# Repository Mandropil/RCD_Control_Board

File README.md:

# RCD_Control_Board
18 Channel PCB with Arduino,  BLE Module, analogue dimming and Cordova App

The board found in the folder "Lichtkasten" can drive up to 18 channels of LED 
with a current limited only by the RCD drivers installed (370ma and 700ma tested) 

The Arduino Nano is driving 3 6 way digital pots with a scale of 256 positions each. 

Digital pots are used for getting non PWM and thus not pulsing lights. 

When the power source is clean, the LEDs are driven wit constand current. 

The <b>AD5206</b> is a 6 channel potentiometer with SPI interface

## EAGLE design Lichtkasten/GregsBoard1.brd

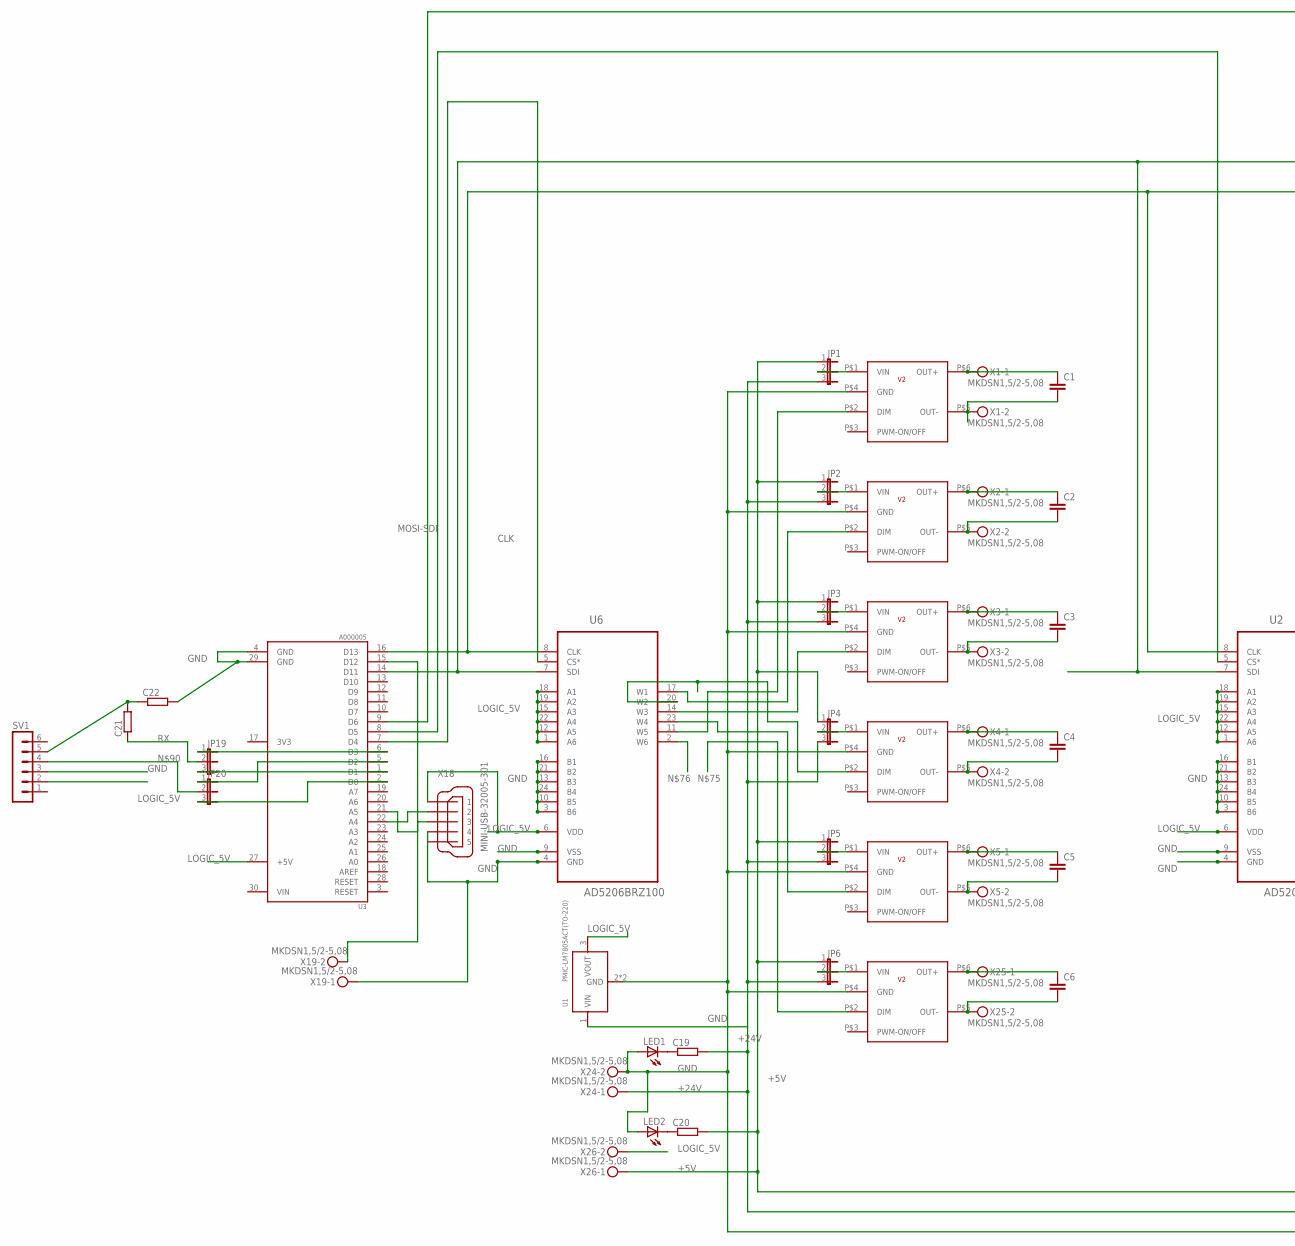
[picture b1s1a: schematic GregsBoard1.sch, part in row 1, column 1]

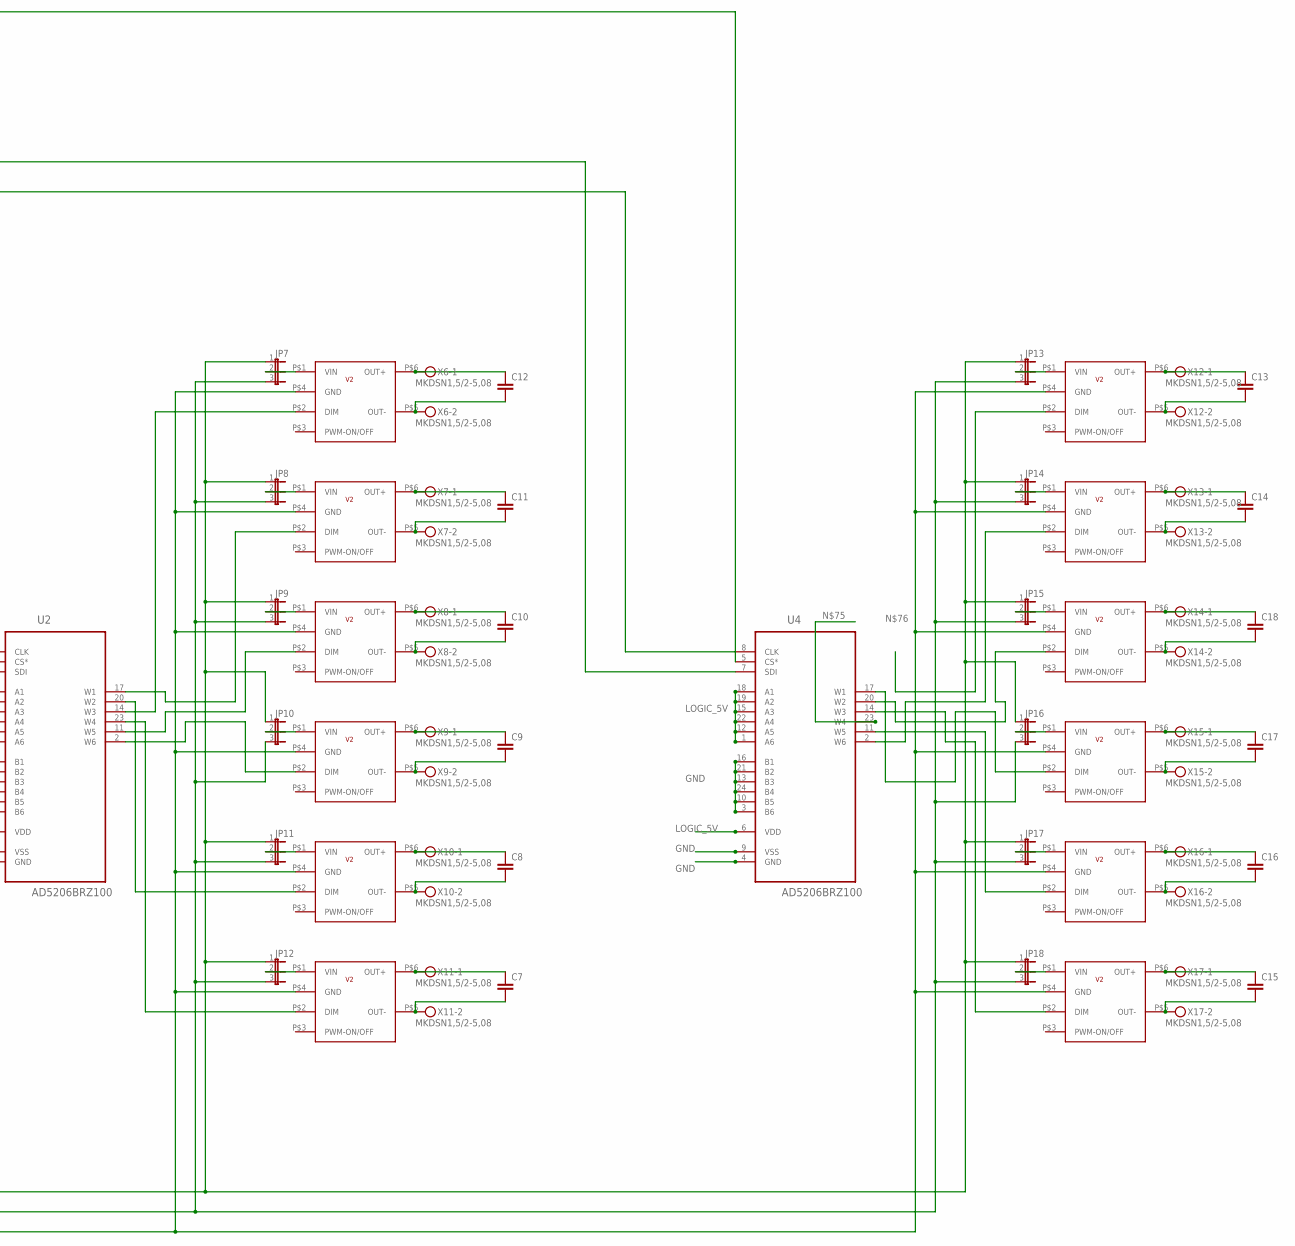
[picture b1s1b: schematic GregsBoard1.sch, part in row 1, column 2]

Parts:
C1, C2, C3, C4, C5, C6, C7, C8, C9, C10, C11, C12, C13, C14, C15, C16, C17, C18: C-EU050-045X075; C050-045X075
C19, C20, C21, C22: R-EU_0207/7; 0207/7
IC1, IC2, IC3, IC4, IC5, IC6, IC7, IC8, IC9, IC10, IC11, IC12, IC13, IC14, IC15, IC16, IC17, IC18: RCD-24_MY_DEV; RCD24-DIP
JP1, JP2, JP3, JP4, JP5, JP6, JP7, JP8, JP9, JP10, JP11, JP12, JP13, JP14, JP15, JP16, JP17, JP18, JP19, JP20: JP2E; JP2
LED1, LED2: LEDB152; Q62902-B152
SV1: MA06-1
U1: PMIC-LM7805ACT(TO-220); TO-220
U2, U4, U6: AD5206BRZ100; SOIC127P1032X265-24N
U3: A000005; ARDUINO_A000005
X1, X2, X3, X4, X5, X6, X7, X8, X9, X10, X11, X12, X13, X14, X15, X16, X17, X19, X24, X25, X26: MKDSN1,5/2-5,08
X18: MINI-USB-32005-301; 32005-301

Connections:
+5V: C20.2, JP1.1, JP2.1, JP3.1, JP4.1, JP5.1, JP6.1, JP7.1, JP8.1, JP9.1, JP10.1, JP11.1, JP12.1, JP13.1, JP14.1, JP15.1, JP16.1, JP17.1, JP18.1, X26.1
+24V: C19.2, JP1.3, JP2.3, JP3.3, JP4.3, JP5.3, JP6.3, JP7.3, JP8.3, JP9.3, JP10.3, JP11.3, JP12.3, JP13.3, JP14.3, JP15.3, JP16.3, JP17.3, JP18.3, U1.1 (VIN), X24.1
CLK: U2.8 (CLK), U3.16 (D13), U4.8 (CLK), U6.8 (CLK)
GND: C22.2, IC1.P$4 (GND), IC2.P$4 (GND), IC3.P$4 (GND), IC4.P$4 (GND), IC5.P$4 (GND), IC6.P$4 (GND), IC7.P$4 (GND), IC8.P$4 (GND), IC9.P$4 (GND), IC10.P$4 (GND), IC11.P$4 (GND), IC12.P$4 (GND), IC13.P$4 (GND), IC14.P$4 (GND), IC15.P$4 (GND), IC16.P$4 (GND), IC17.P$4 (GND), IC18.P$4 (GND), LED1.A, LED2.A, SV1.3, U1.2 (GND), U1.HEAT (GND), U2.3 (B6), U2.4 (GND), U2.9 (VSS), U2.10 (B5), U2.13 (B3), U2.16 (B1), U2.21 (B2), U2.24 (B4), U3.4 (GND), U3.29 (GND), U4.3 (B6), U4.4 (GND), U4.9 (VSS), U4.10 (B5), U4.13 (B3), U4.16 (B1), U4.21 (B2), U4.24 (B4), U6.3 (B6), U6.4 (GND), U6.9 (VSS), U6.10 (B5), U6.13 (B3), U6.16 (B1), U6.21 (B2), U6.24 (B4), X18.4, X19.1, X24.2
LOGIC_5V: SV1.2, U1.3 (VOUT), U2.1 (A6), U2.6 (VDD), U2.12 (A5), U2.15 (A3), U2.18 (A1), U2.19 (A2), U2.22 (A4), U3.27 (+5V), U4.1 (A6), U4.6 (VDD), U4.12 (A5), U4.15 (A3), U4.18 (A1), U4.19 (A2), U4.22 (A4), U6.1 (A6), U6.6 (VDD), U6.12 (A5), U6.15 (A3), U6.18 (A1), U6.19 (A2), U6.22 (A4), X18.1, X26.2
MOSI-SDI: U2.7 (SDI), U3.14 (D11), U4.7 (SDI), U6.7 (SDI)
unnamed: C6.1, IC1.P$6 (OUT+), X25.1
unnamed: C6.2, IC1.P$5 (OUT-), X25.2
unnamed: C1.1, IC2.P$6 (OUT+), X1.1
unnamed: C1.2, IC2.P$5 (OUT-), X1.2
unnamed: C2.1, IC3.P$6 (OUT+), X2.1
unnamed: C2.2, IC3.P$5 (OUT-), X2.2
unnamed: C3.1, IC4.P$6 (OUT+), X3.1
unnamed: C3.2, IC4.P$5 (OUT-), X3.2
unnamed: C4.1, IC5.P$6 (OUT+), X4.1
unnamed: C4.2, IC5.P$5 (OUT-), X4.2
unnamed: C5.1, IC6.P$6 (OUT+), X5.1
unnamed: C5.2, IC6.P$5 (OUT-), X5.2
unnamed: IC2.P$2 (DIM), U6.11 (W5)
unnamed: IC3.P$2 (DIM), U6.17 (W1)
unnamed: IC4.P$2 (DIM), U6.14 (W3)
unnamed: IC5.P$2 (DIM), U6.20 (W2)
unnamed: IC6.P$2 (DIM), U6.23 (W4)
unnamed: U3.22 (A4), X18.2
unnamed: IC2.P$1 (VIN), JP1.2
unnamed: IC3.P$1 (VIN), JP2.2
unnamed: IC4.P$1 (VIN), JP3.2
unnamed: IC5.P$1 (VIN), JP4.2
unnamed: IC6.P$1 (VIN), JP5.2
unnamed: IC1.P$1 (VIN), JP6.2
unnamed: U3.7 (D4), U6.5 (CS*)
unnamed: U2.5 (CS*), U3.8 (D5)
unnamed: C12.1, IC7.P$6 (OUT+), X6.1
unnamed: C12.2, IC7.P$5 (OUT-), X6.2
unnamed: C11.1, IC8.P$6 (OUT+), X7.1
unnamed: C11.2, IC8.P$5 (OUT-), X7.2
unnamed: C10.1, IC9.P$6 (OUT+), X8.1
unnamed: C10.2, IC9.P$5 (OUT-), X8.2
unnamed: C9.1, IC10.P$6 (OUT+), X9.1
unnamed: C9.2, IC10.P$5 (OUT-), X9.2
unnamed: C8.1, IC11.P$6 (OUT+), X10.1
unnamed: C8.2, IC11.P$5 (OUT-), X10.2
unnamed: C7.1, IC12.P$6 (OUT+), X11.1
unnamed: C7.2, IC12.P$5 (OUT-), X11.2
unnamed: IC7.P$2 (DIM), U2.14 (W3)
unnamed: IC8.P$2 (DIM), U2.17 (W1)
unnamed: IC9.P$2 (DIM), U2.11 (W5)
unnamed: IC10.P$2 (DIM), U2.2 (W6)
unnamed: IC11.P$2 (DIM), U2.20 (W2)
unnamed: IC12.P$2 (DIM), U2.23 (W4)
unnamed: IC7.P$1 (VIN), JP7.2
unnamed: IC8.P$1 (VIN), JP8.2
unnamed: IC9.P$1 (VIN), JP9.2
unnamed: IC10.P$1 (VIN), JP10.2
unnamed: IC11.P$1 (VIN), JP11.2
unnamed: IC12.P$1 (VIN), JP12.2
unnamed: U3.9 (D6), U4.5 (CS*)
unnamed: C18.1, IC15.P$6 (OUT+), X14.1
unnamed: C13.1, IC13.P$6 (OUT+), X12.1
unnamed: C13.2, IC13.P$5 (OUT-), X12.2
unnamed: C14.1, IC14.P$6 (OUT+), X13.1
unnamed: C14.2, IC14.P$5 (OUT-), X13.2
unnamed: C18.2, IC15.P$5 (OUT-), X14.2
unnamed: C17.1, IC16.P$6 (OUT+), X15.1
unnamed: C17.2, IC16.P$5 (OUT-), X15.2
unnamed: U3.15 (D12), X19.2
unnamed: C16.1, IC17.P$6 (OUT+), X16.1
unnamed: C16.2, IC17.P$5 (OUT-), X16.2
unnamed: C15.1, IC18.P$6 (OUT+), X17.1
unnamed: C15.2, IC18.P$5 (OUT-), X17.2
unnamed: U3.21 (A5), X18.3
unnamed: IC14.P$2 (DIM), U4.2 (W6)
unnamed: IC15.P$2 (DIM), U4.20 (W2)
unnamed: IC16.P$2 (DIM), U4.17 (W1)
unnamed: IC17.P$2 (DIM), U4.11 (W5)
unnamed: IC18.P$2 (DIM), U4.14 (W3)
unnamed: IC13.P$1 (VIN), JP13.2
unnamed: IC14.P$1 (VIN), JP14.2
unnamed: C19.1, LED1.K (C)
unnamed: C20.1, LED2.K (C)
unnamed: IC1.P$2 (DIM), U4.23 (W4)
unnamed: IC13.P$2 (DIM), U6.2 (W6)
unnamed: IC15.P$1 (VIN), JP15.2
unnamed: IC16.P$1 (VIN), JP16.2
unnamed: IC17.P$1 (VIN), JP17.2
unnamed: IC18.P$1 (VIN), JP18.2
unnamed: JP19.3, U3.1 (D1)
unnamed: JP19.1, U3.6 (D3)
unnamed: C21.1, JP19.2
unnamed: JP20.1, U3.5 (D2)
unnamed: JP20.2, SV1.4
RX: C21.2, C22.1, SV1.5
TX: JP20.3, U3.2 (D0)
VIN: U3.30 (VIN)

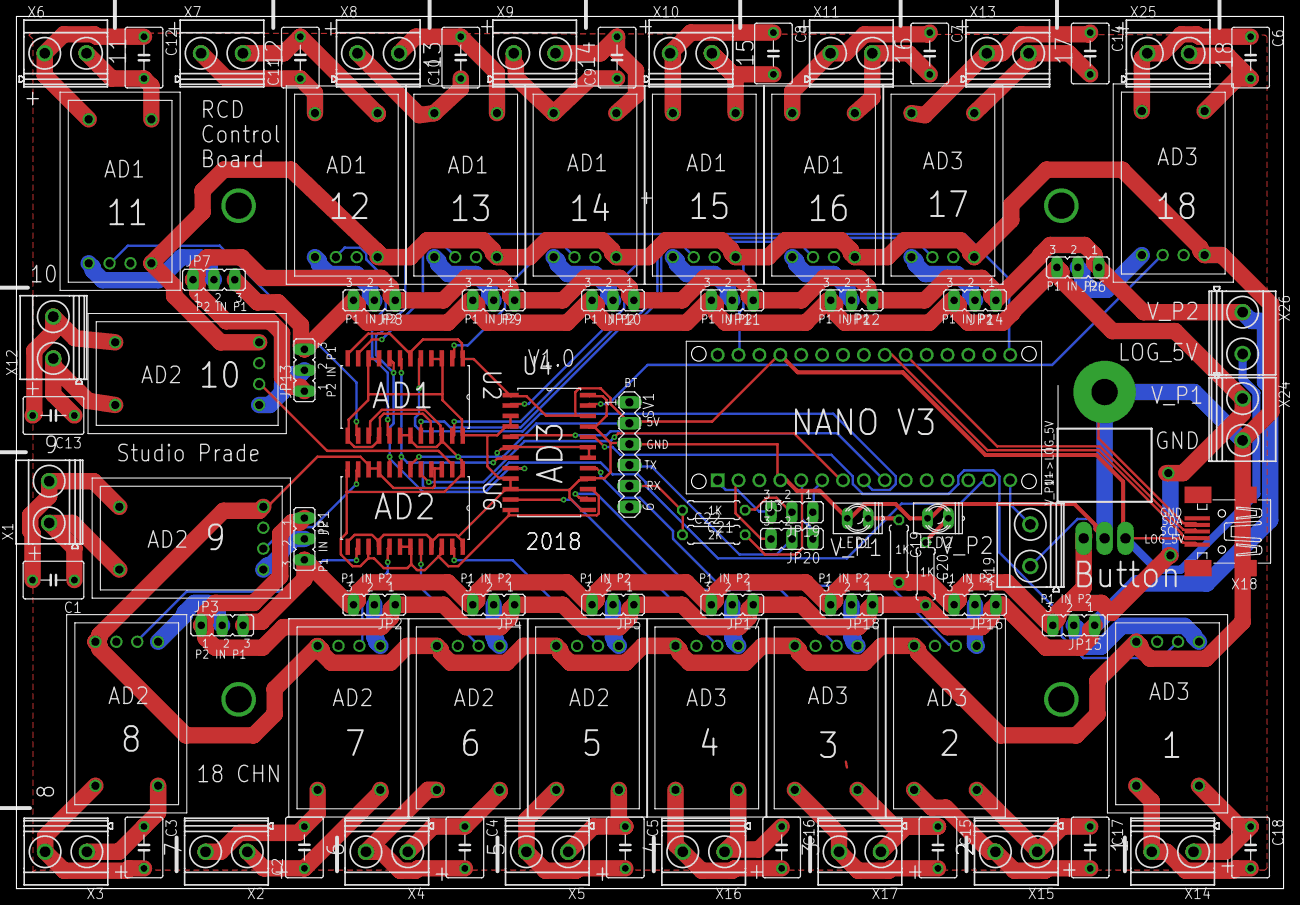
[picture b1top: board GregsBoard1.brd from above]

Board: 2 copper layers, 154.0 x 106.0 mm, 90 parts (0 on the bottom side), 93 nets.

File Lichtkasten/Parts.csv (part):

Partlist

Exported from GregsBoard1.brd at 01.02.2018 22:38

EAGLE Version 8.6.0 Copyright (c) 1988-2018 Autodesk, Inc.

Assembly variant: 

Part     Value                  Package              Library                Position (mm)         Orientation

C1                              C050-045X075         resistor               (4.5 37.5)            R180
C2                              C050-045X075         resistor               (35 5)                R90
C3                              C050-045X075         resistor               (15.5 5)              R270
C4                              C050-045X075         resistor               (54.5 5)              R270
C5                              C050-045X075         resistor               (74 5)                R270
C6                              C050-045X075         resistor               (150 101)             R270
C7                              C050-045X075         resistor               (111 101.5)           R270
C8                              C050-045X075         resistor               (92 101.5)            R270
C9                              C050-045X075         resistor               (73 101)              R90
C10                             C050-045X075         resistor               (54 101)              R90
C11                             C050-045X075         resistor               (34.5 101)            R90
C12                             C050-045X075         resistor               (15.5 101)            R270
C13                             C050-045X075         resistor               (4.5 57.5)            R180
C14                             C050-045X075         resistor               (130.5 101.5)         R270
C15                             C050-045X075         resistor               (112 5)               R270
C16                             C050-045X075         resistor               (93 5)                R270
C17                             C050-045X075         resistor               (130.5 5)             R270
C18                             C050-045X075         resistor               (150 5)               R270
C19                             0207/7               resistor               (107.25 41)           R270
C20                             0207/7               resistor               (110.5 38.25)         R270
C21                             0207/7               resistor               (84.75 46)            R180
C22                             0207/7               resistor               (84.75 43)            R0
IC1      RCD-24_MY_DEV          RCD24-DIP            RCD-Custom1            (140.5 86)            R90
IC2      RCD-24_MY_DEV          RCD24-DIP            RCD-Custom1            (21 42.5)             R180
IC3      RCD-24_MY_DEV          RCD24-DIP            RCD-Custom1            (40.5 20.5)           R270
IC4      RCD-24_MY_DEV          RCD24-DIP            RCD-Custom1            (13.5 21)             R270
IC5      RCD-24_MY_DEV          RCD24-DIP            RCD-Custom1            (55 20.5)             R270
IC6      RCD-24_MY_DEV          RCD24-DIP            RCD-Custom1            (69.5 20.5)           R270
IC7      RCD-24_MY_DEV          RCD24-DIP            RCD-Custom1            (12.5 85)             R90
IC8      RCD-24_MY_DEV          RCD24-DIP            RCD-Custom1            (40 85.75)            R90
IC9      RCD-24_MY_DEV          RCD24-DIP            RCD-Custom1            (54.5 85.75)          R90
IC10     RCD-24_MY_DEV          RCD24-DIP            RCD-Custom1            (69 85.75)            R90
IC11     RCD-24_MY_DEV          RCD24-DIP            RCD-Custom1            (83.5 85.75)          R90
IC12     RCD-24_MY_DEV          RCD24-DIP            RCD-Custom1            (98 85.75)            R90
IC13     RCD-24_MY_DEV          RCD24-DIP            RCD-Custom1            (20.5 62.5)           R180
IC14     RCD-24_MY_DEV          RCD24-DIP            RCD-Custom1            (112.5 85.75)         R90
IC15     RCD-24_MY_DEV          RCD24-DIP            RCD-Custom1            (140 21)              R270
IC16     RCD-24_MY_DEV          RCD24-DIP            RCD-Custom1            (113 20.5)            R270
IC17     RCD-24_MY_DEV          RCD24-DIP            RCD-Custom1            (84 20.5)             R270
IC18     RCD-24_MY_DEV          RCD24-DIP            RCD-Custom1            (98.5 20.5)           R270
JP1                             JP2                  jumper                 (35 42.5)             R270
JP2                             JP2                  jumper                 (43.5 34.5)           R180
JP3                             JP2                  jumper                 (25 32)               R0
JP4                             JP2                  jumper                 (58 34.5)             R180
JP5                             JP2                  jumper                 (72.5 34.5)           R180
JP6                             JP2                  jumper                 (129 75.5)            R180
JP7                             JP2                  jumper                 (24 74)               R0
JP8                             JP2                  jumper                 (43.5 71.5)           R180
JP9                             JP2                  jumper                 (58 71.5)             R180
JP10                            JP2                  jumper                 (72.5 71.5)           R180
JP11                            JP2                  jumper                 (87 71.5)             R180
JP12                            JP2                  jumper                 (101.5 71.5)          R180
JP13                            JP2                  jumper                 (35 63)               R90
JP14                            JP2                  jumper                 (116.5 71.5)          R180
JP15                            JP2                  jumper                 (128.5 32)            R180
JP16                            JP2                  jumper                 (116.5 34.5)          R180
JP17                            JP2                  jumper                 (87 34.5)             R180
JP18                            JP2                  jumper                 (101.5 34.5)          R180
LED1                            Q62902-B152          led                    (102.25 45)           R180
LED2                            Q62902-B152          led                    (112 45)              R180
SV1                             MA06-1               con-lstb               (74.5 52.75)          R270
U1       PMIC-LM7805ACT(TO-220) TO-220               PMIC-LM7805ACT_TO-220_ (132.25 54)           R0
U2       AD5206BRZ100           SOIC127P1032X265-24N AD5206BRZ100           (47.25 59.75)         R270
U3       A000005                ARDUINO_A000005      A000005                (103 57.25)           R90
U4       AD5206BRZ100           SOIC127P1032X265-24N AD5206BRZ100           (64.75 53)            R0
U6       AD5206BRZ100           SOIC127P1032X265-24N AD5206BRZ100           (47.25 46.25)         R270
X1       MKDSN1,5/2-5,08        MKDSN1,5/2-5,08      con-phoenix-508        (4 47)                R90
X2       MKDSN1,5/2-5,08        MKDSN1,5/2-5,08      con-phoenix-508        (25.5 4.5)            R180
X3       MKDSN1,5/2-5,08        MKDSN1,5/2-5,08      con-phoenix-508        (6 4.5)               R180
X4       MKDSN1,5/2-5,08        MKDSN1,5/2-5,08      con-phoenix-508        (45 4.5)              R180
X5       MKDSN1,5/2-5,08        MKDSN1,5/2-5,08      con-phoenix-508        (64.5 4.5)            R180
X6       MKDSN1,5/2-5,08        MKDSN1,5/2-5,08      con-phoenix-508        (6 101.5)             R0
X7       MKDSN1,5/2-5,08        MKDSN1,5/2-5,08      con-phoenix-508        (25 101.5)            R0
X8       MKDSN1,5/2-5,08        MKDSN1,5/2-5,08      con-phoenix-508        (44 101.5)            R0
X9       MKDSN1,5/2-5,08        MKDSN1,5/2-5,08      con-phoenix-508        (63 101.5)            R0
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
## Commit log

2018-03-09 Initial Upload
2018-03-09 Eagle Schematics and Board added
2018-03-13 Update mit ON/OFF
2018-03-15 Farben geändert
2018-03-19 added ON/OFF, borders for non selected
2018-03-25 Changes after Android Version troubles
2018-04-05 Changed some design stuff and buttons
2018-04-05 Slider scale, border design, names
2018-04-05 Built Android Project
2018-04-05 Compiled project
2018-04-30 Removed test boxes
2018-04-30 added Android App File in root
2018-04-30 Moved Android App to root
